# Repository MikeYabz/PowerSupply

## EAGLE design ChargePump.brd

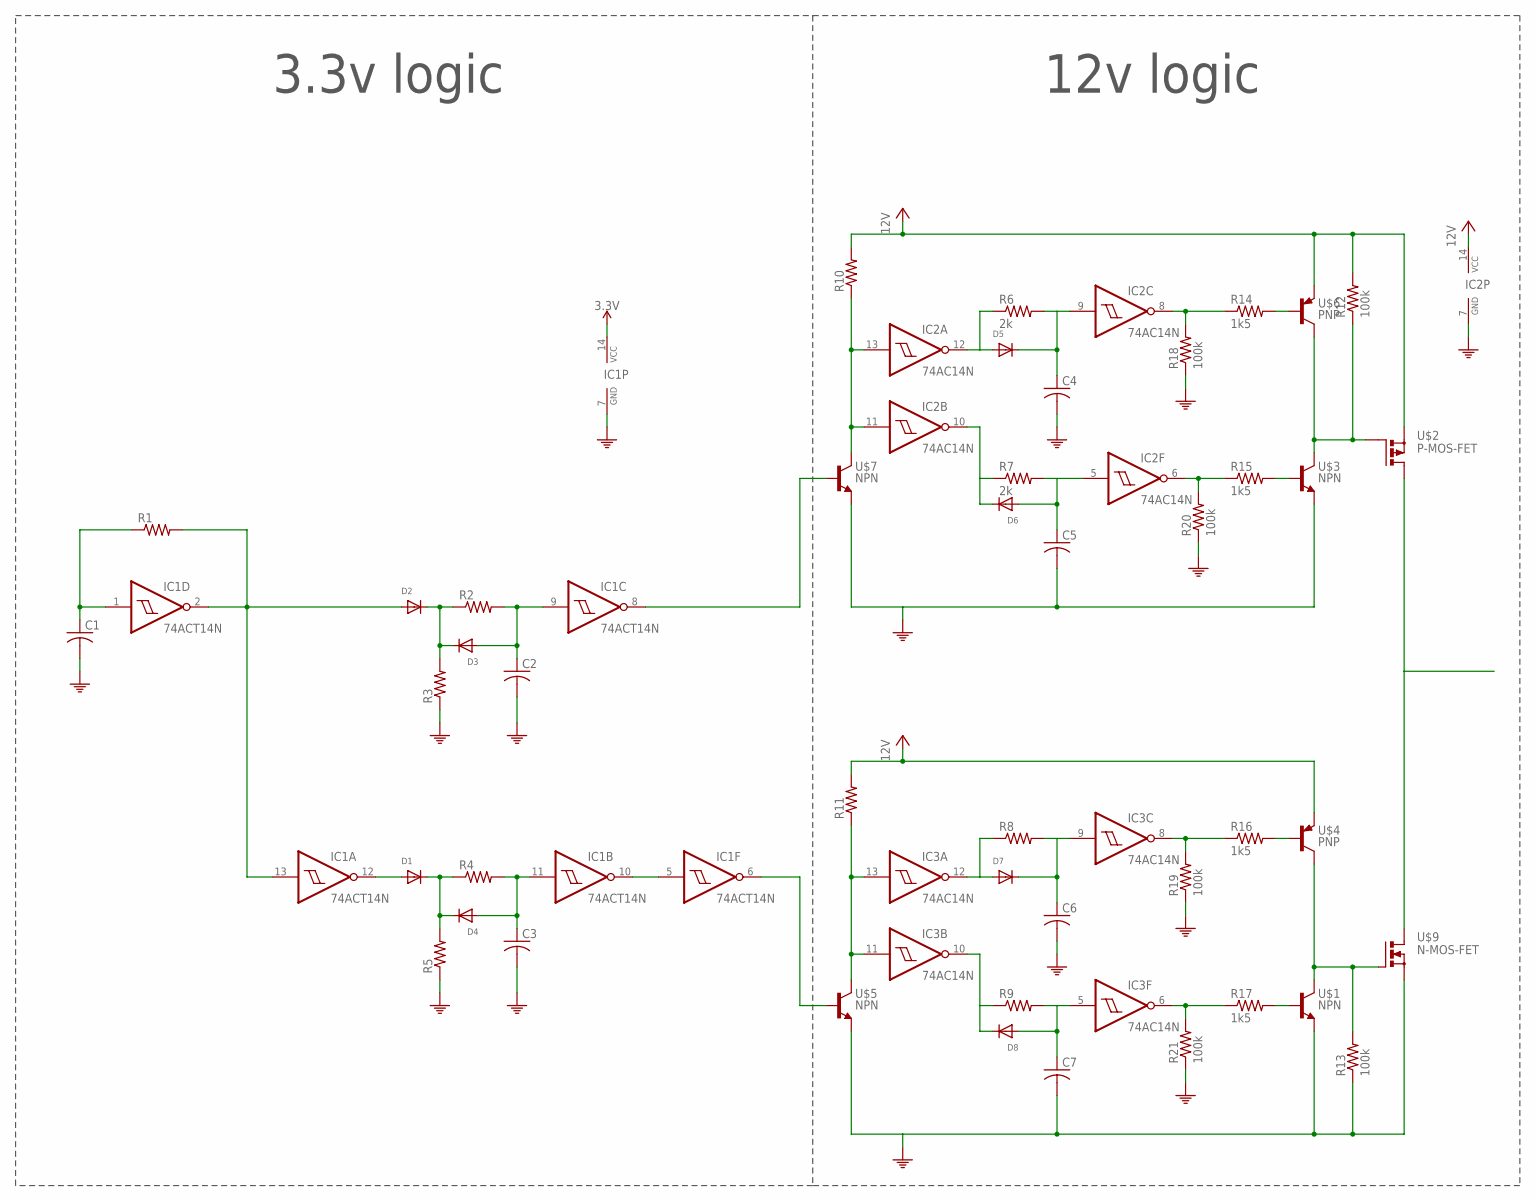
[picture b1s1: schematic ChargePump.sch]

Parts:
C1, C2, C3, C4, C5, C6, C7: C-USC0603; C0603
D1, D2, D3, D4, D5, D6, D7, D8: DIODEDO-1N4148; DO-1N4148
IC1: 74ACT14N; DIL14
IC2, IC3: 74AC14N; DIL14
R1, R2, R3, R4, R5, R8, R9, R10, R11: R-US_R0603; R0603
R6, R7: 2k; R0603
R12, R13, R18, R19, R20, R21: 100k; R0603
R14, R15, R16, R17: 1k5; R0603
U$1, U$3, U$5, U$7: NPN; SOT23
U$2: P-MOS-FET; SOT23
U$4, U$6: PNP; SOT23
U$9: N-MOS-FET; SOT23

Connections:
3.3V: IC1.14 (VCC)
+12V: IC2.14 (VCC), R10.2, R11.2, R12.2, U$2.C (S), U$4.E, U$6.E
GND: C1.2, C2.2, C3.2, C4.2, C5.2, C6.2, C7.2, IC1.7 (GND), IC2.7 (GND), IC3.7 (GND), R3.1, R5.1, R13.1, R18.1, R19.1, R20.1, R21.1, U$1.E, U$3.E, U$5.E, U$7.E, U$9.E (S)
unnamed: D2.A, IC1.2 (O), IC1.13 (I), R1.2
unnamed: C1.1, IC1.1 (I), R1.1
unnamed: D1.A, IC1.12 (O)
unnamed: D2.C, D3.C, R2.1, R3.2
unnamed: D1.C, D4.C, R4.1, R5.2
unnamed: C2.1, D3.A, IC1.9 (I), R2.2
unnamed: C3.1, D4.A, IC1.11 (I), R4.2
unnamed: IC1.5 (I), IC1.10 (O)
unnamed: R12.1, U$2.B (G), U$3.C, U$6.C
unnamed: R13.2, U$1.C, U$4.C, U$9.B (G)
unnamed: IC1.8 (O), U$7.B
unnamed: D5.A, IC2.12 (O), R6.1
unnamed: IC2.11 (I), IC2.13 (I), R10.1, U$7.C
unnamed: D7.A, IC3.12 (O), R8.1
unnamed: D6.C, IC2.10 (O), R7.1
unnamed: C6.1, D7.C, IC3.9 (I), R8.2
unnamed: C7.1, D8.A, IC3.5 (I), R9.2
unnamed: C4.1, D5.C, IC2.9 (I), R6.2
unnamed: C5.1, D6.A, IC2.5 (I), R7.2
unnamed: IC2.8 (O), R14.1, R18.2
unnamed: R14.2, U$6.B
unnamed: U$2.E (D), U$9.C (D)
unnamed: IC2.6 (O), R15.1, R20.2
unnamed: R15.2, U$3.B
unnamed: IC1.6 (O), U$5.B
unnamed: IC3.11 (I), IC3.13 (I), R11.1, U$5.C
unnamed: D8.C, IC3.10 (O), R9.1
unnamed: IC3.8 (O), R16.1, R19.2
unnamed: R16.2, U$4.B
unnamed: IC3.6 (O), R17.1, R21.2
unnamed: R17.2, U$1.B
VCC: IC3.14 (VCC)

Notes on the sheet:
3.3v logic
12v logic

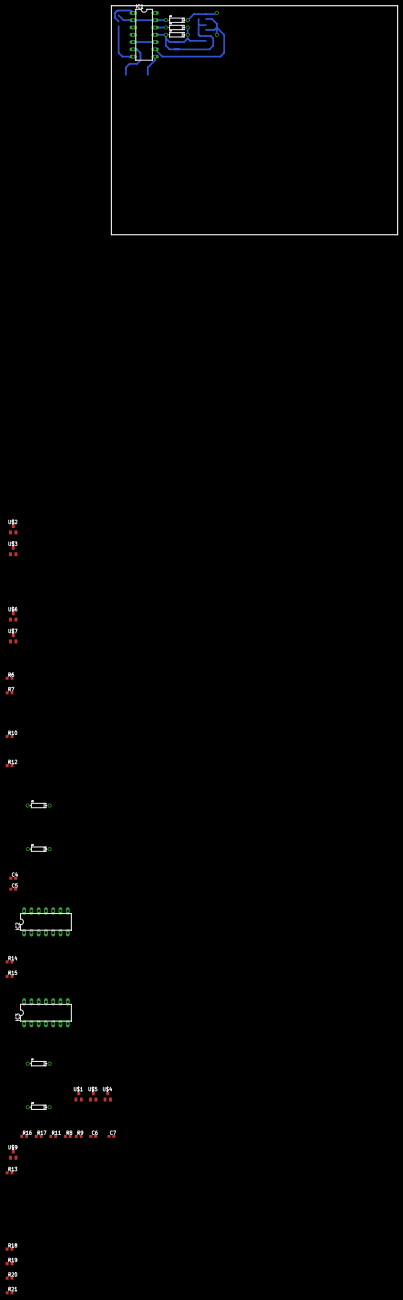
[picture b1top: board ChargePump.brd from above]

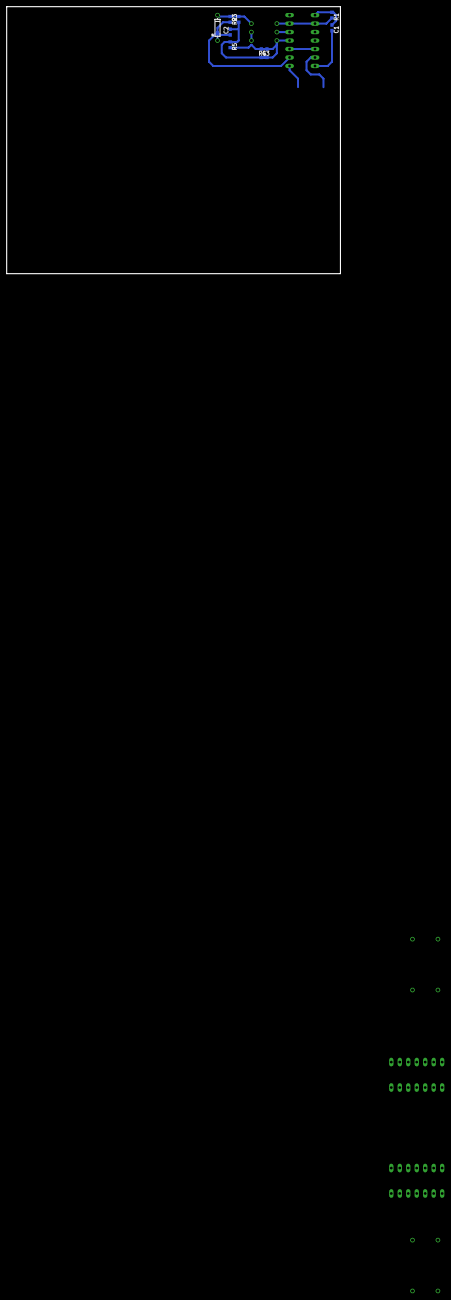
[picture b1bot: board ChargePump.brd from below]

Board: 2 copper layers, 100.0 x 80.0 mm, 47 parts (9 on the bottom side), 33 nets.

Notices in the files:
parts and their libraries:
SparkFun-PowerSymbols: Licensing: Creative Commons ShareAlike 4.0 International - https://creativecommons.org/licenses/by-sa/4.0
